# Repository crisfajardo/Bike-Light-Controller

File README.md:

# 🚲 Bike-Light-Controller (Smart Cycling System)

This repository hosts a specialized embedded system designed for conventional bicycles, developed as a final project for my **Bachelor's Degree in Electronic and Telecommunications Engineering**.

The system transforms a standard bike into a "smart" vehicle by automating safety lighting through real-time sensor data fusion.

---

## 🚀 Overview
The **Bike-Light-Controller** manages visibility and signaling automatically. Using an **ESP32-S3** and the **Arduino IDE** framework, the system processes environmental light levels and motion dynamics to ensure rider safety.

### ✨ Key Features
* **Intelligent Brake Light:** Automatically triggers high-intensity rear LEDs when deceleration is detected via the **MPU6050**.
* **Adaptive Headlight:** Adjusts front lighting based on ambient lux levels measured by the **TEMT6000**.
* **Custom Hardware:** Professional PCB designed using **KiCad 9.0**, utilizing official **Espressif hardware libraries** for the ESP32-S3.
* **Real-time Processing:** Low-latency response to motion and lighting changes.

---

## 🛠️ Tech Stack

### Hardware Components
| Component | Function |
| :--- | :--- |
| **MCU** | **ESP32-S3** (Xtensa® 32-bit LX7 Dual-Core) |
| **IMU** | **MPU6050** (6-axis Accelerometer & Gyroscope) |
| **Light Sensor** | **TEMT6000** (High-precision ambient light sensor) |
| **PCB Design** | **KiCad 9.0** (Schematic & Layout) |

### Software & Firmware
* **Language:** C++ / Arduino Framework
* **IDE:** Arduino IDE 2.3.8
* **Communication:** I2C Protocol (Sensors) / MQTT (Optional for IoT telemetry)
* **Libraries:** `Adafruit_MPU6050`, `Adafruit_Sensor`, `Wire.h`

---

## 📂 Repository Structure

```text
├── Firmware/        # Source code (.ino) for the ESP32-S3
├── Hardware/        # KiCad 9.0 Project files (Schematics, PCB, Gerbers)
├── Docs/            # Datasheets, project report, and bibliography
└── Assets/          # Images, circuit diagrams, and 3D renders

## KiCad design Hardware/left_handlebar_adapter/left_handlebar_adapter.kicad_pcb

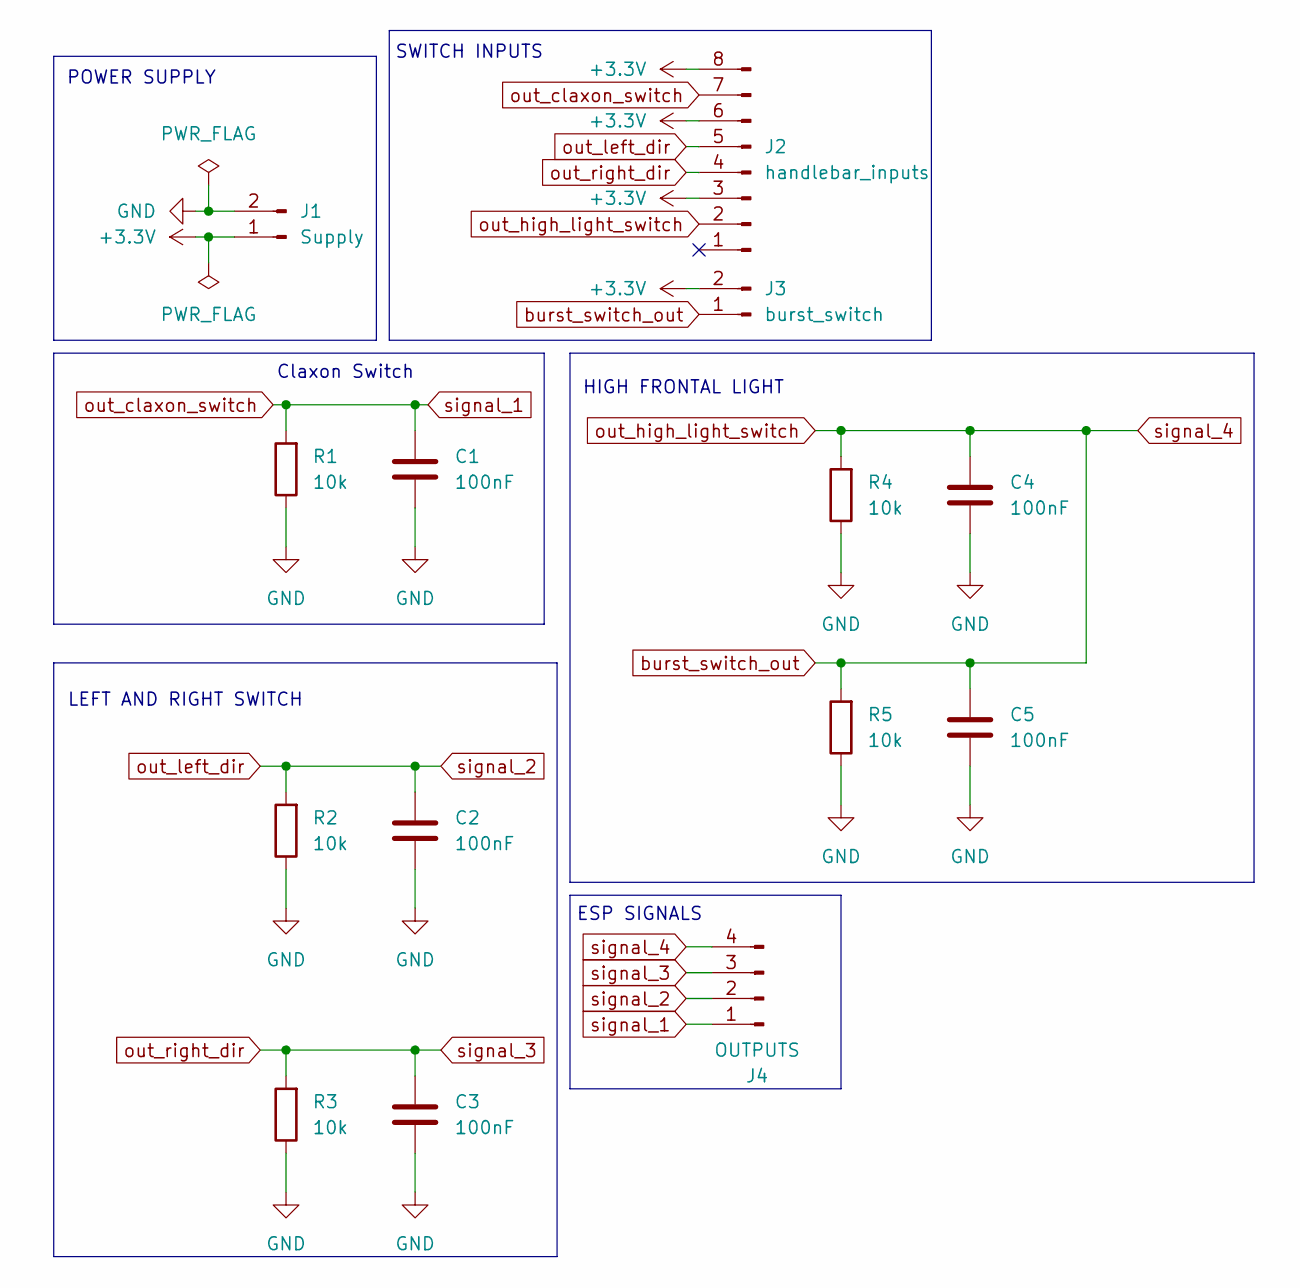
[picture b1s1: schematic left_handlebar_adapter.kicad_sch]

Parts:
C1, C2, C3, C4, C5: 100nF; C_Disc_D5.0mm_W2.5mm_P2.50mm
J1: Supply; PinHeader_1x02_P2.54mm_Vertical
J2: handlebar_inputs; PinHeader_1x08_P2.54mm_Vertical
J3: burst_switch; PinHeader_1x02_P2.54mm_Vertical
J4: OUTPUTS; PinHeader_1x04_P2.54mm_Vertical
R1, R2, R3, R4, R5: 10k; R_Axial_DIN0207_L6.3mm_D2.5mm_P7.62mm_Horizontal

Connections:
+3.3V: J1.1, J2.3, J2.6, J2.8, J3.2
GND: C1.2, C2.2, C3.2, C4.2, C5.2, J1.2, R1.1, R2.1, R3.1, R4.1, R5.1
burst_switch_out: C4.1, C5.1, J2.2, J3.1, J4.4, R4.2, R5.2
out_claxon_switch: C1.1, J2.7, J4.1, R1.2
out_left_dir: C2.1, J2.5, J4.2, R2.2
out_right_dir: C3.1, J2.4, J4.3, R3.2

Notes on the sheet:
POWER SUPPLY
ESP SIGNALS
SWITCH INPUTS
HIGH FRONTAL LIGHT
Claxon Switch
LEFT AND RIGHT SWITCH

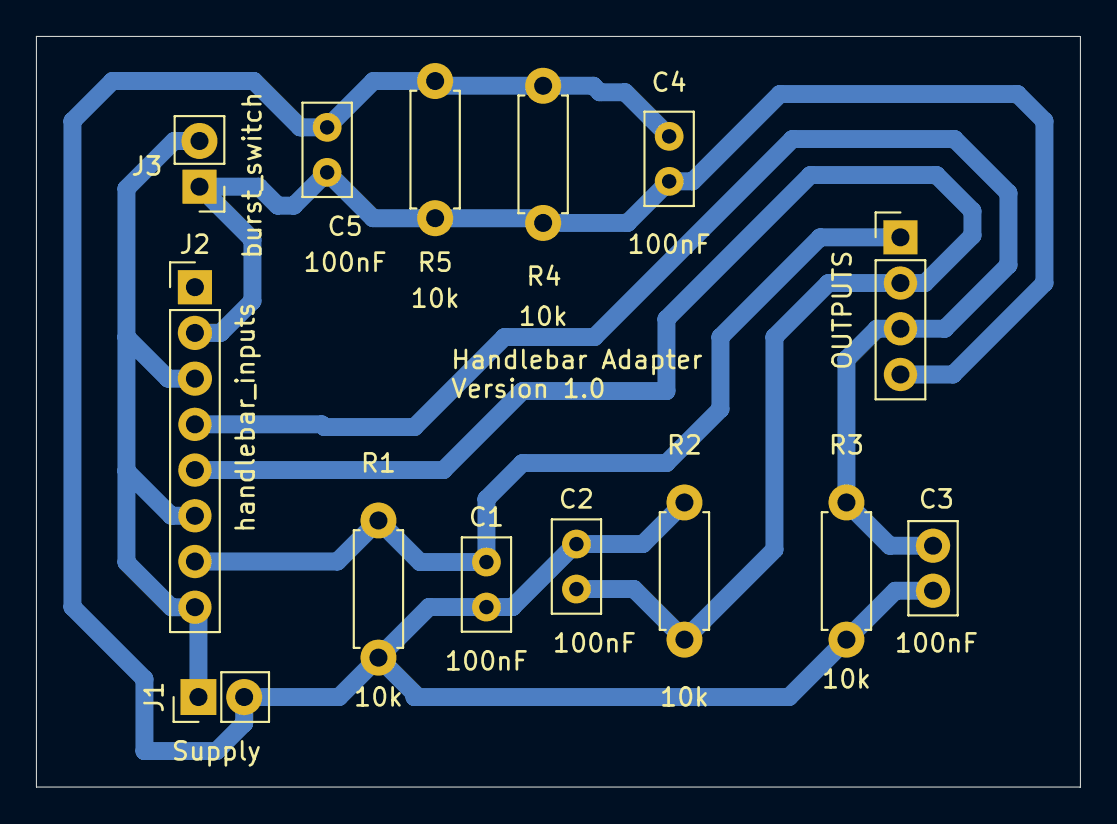
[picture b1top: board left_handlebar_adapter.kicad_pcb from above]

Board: 2 copper layers, 58.0 x 41.7 mm, 14 parts (0 on the bottom side), 6 nets.

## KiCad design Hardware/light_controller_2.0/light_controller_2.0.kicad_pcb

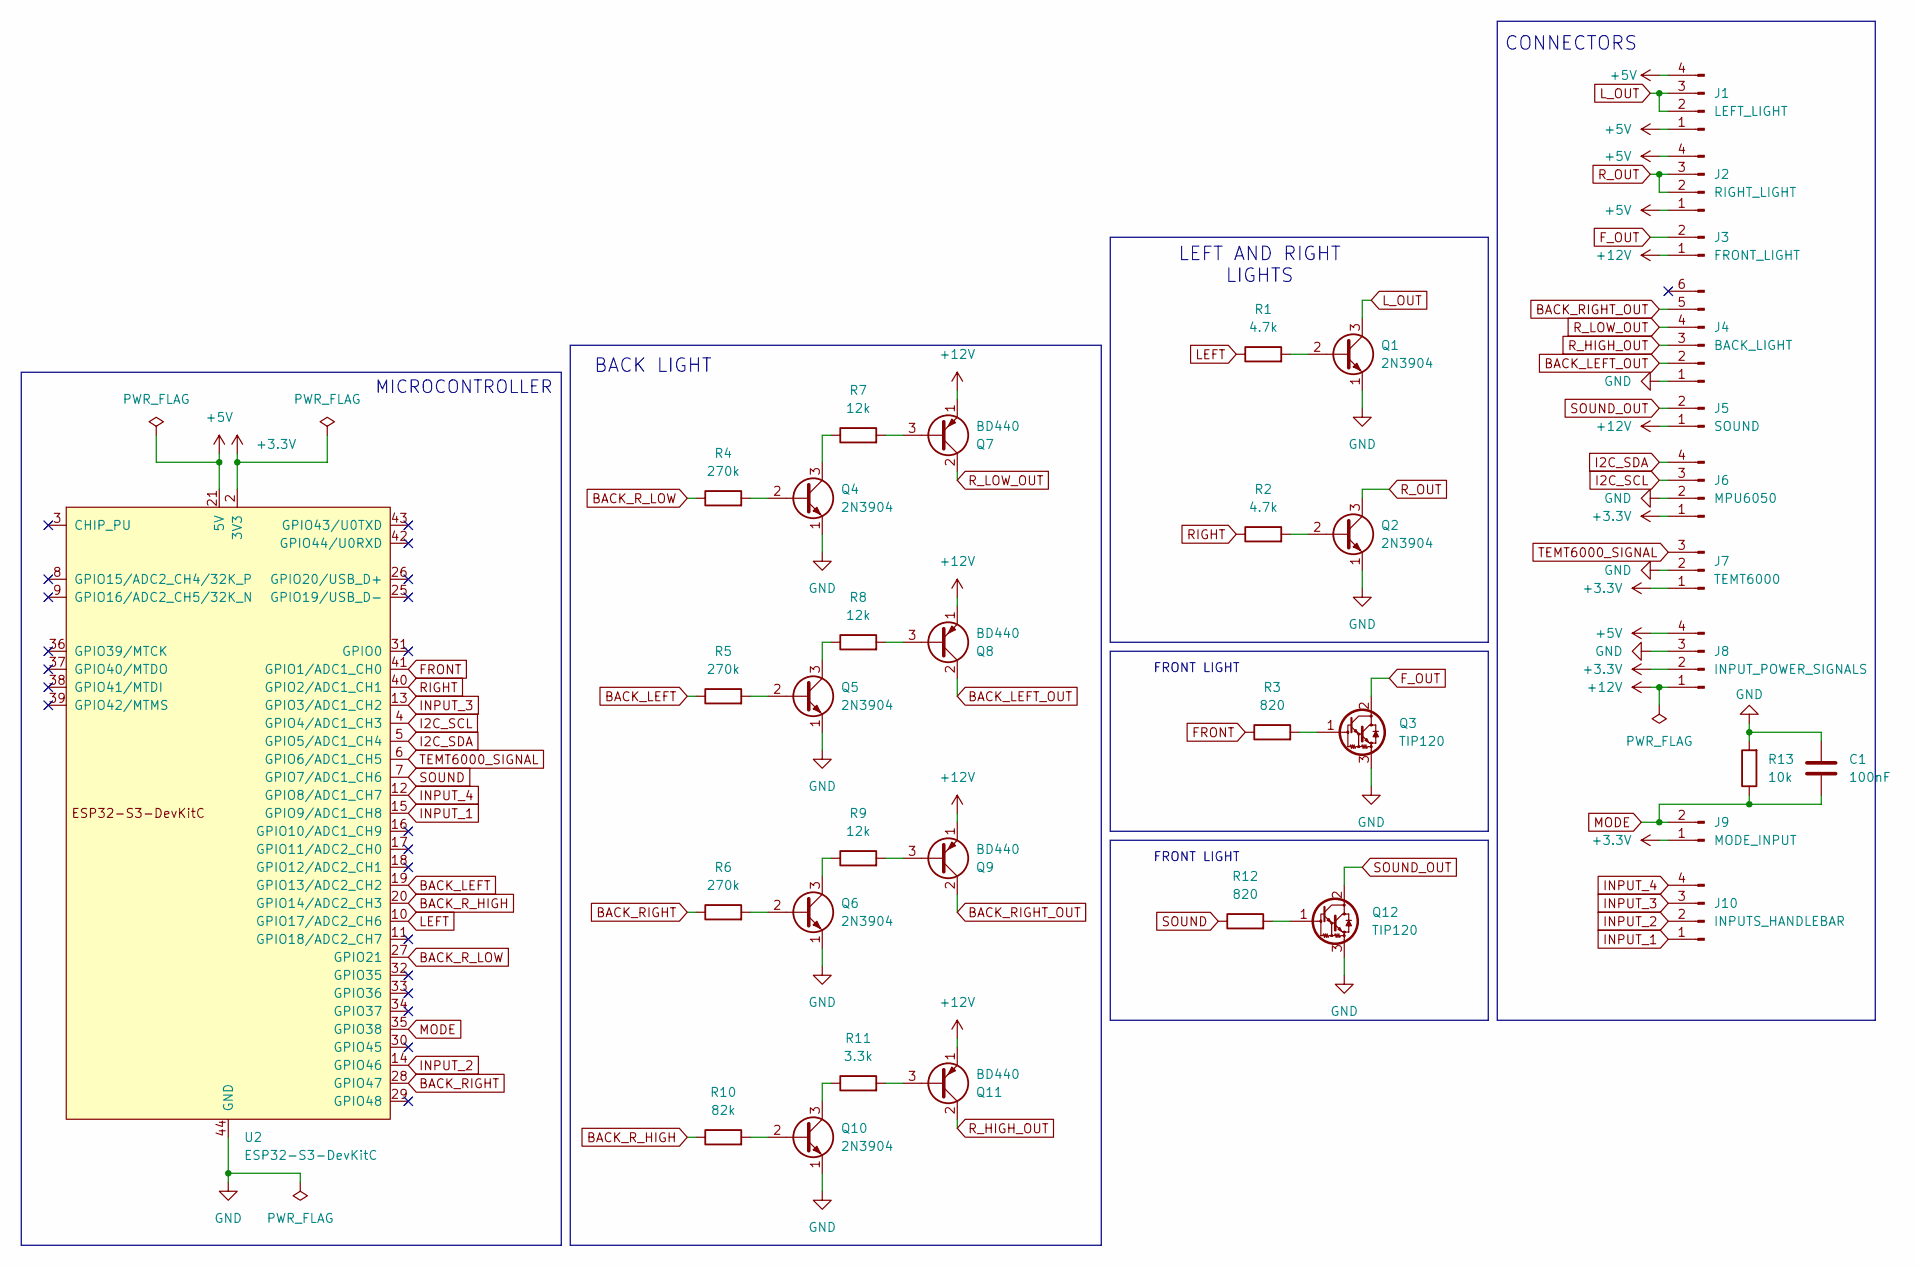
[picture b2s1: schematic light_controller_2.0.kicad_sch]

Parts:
C1: 100nF; C_Disc_D5.0mm_W2.5mm_P2.50mm
J1: LEFT_LIGHT; PinHeader_1x04_P2.54mm_Vertical
J2: RIGHT_LIGHT; PinHeader_1x04_P2.54mm_Vertical
J3: FRONT_LIGHT; PinHeader_1x02_P2.54mm_Vertical
J4: BACK_LIGHT; PinHeader_1x06_P2.54mm_Vertical
J5: SOUND; PinHeader_1x02_P2.54mm_Vertical
J6: MPU6050; PinHeader_1x04_P2.54mm_Vertical
J7: TEMT6000; PinHeader_1x03_P2.54mm_Vertical
J8: INPUT_POWER_SIGNALS; PinHeader_1x04_P2.54mm_Vertical
J9: MODE_INPUT; PinHeader_1x02_P2.54mm_Vertical
J10: INPUTS_HANDLEBAR; PinHeader_1x04_P2.54mm_Vertical
Q1, Q2, Q4, Q5, Q6, Q10: 2N3904; TO-92_Inline_Wide
Q3, Q12: TIP120; TO-220-3_Vertical
Q7, Q8, Q9, Q11: BD440; TO-126-3_Vertical
R1, R2: 4.7k; R_Axial_DIN0207_L6.3mm_D2.5mm_P7.62mm_Horizontal
R3, R12: 820; R_Axial_DIN0207_L6.3mm_D2.5mm_P7.62mm_Horizontal
R4, R5, R6: 270k; R_Axial_DIN0207_L6.3mm_D2.5mm_P7.62mm_Horizontal
R7, R8, R9: 12k; R_Axial_DIN0207_L6.3mm_D2.5mm_P7.62mm_Horizontal
R10: 82k; R_Axial_DIN0207_L6.3mm_D2.5mm_P7.62mm_Horizontal
R11: 3.3k; R_Axial_DIN0207_L6.3mm_D2.5mm_P7.62mm_Horizontal
R13: 10k; R_Axial_DIN0207_L6.3mm_D2.5mm_P7.62mm_Horizontal
U2: ESP32-S3-DevKitC

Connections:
+3.3V: J6.1, J7.1, J8.2, J9.1, U2.1 (3V3), U2.2 (3V3)
+5V: J1.1, J1.4, J2.1, J2.4, J8.4, U2.21 (5V)
+12V: J3.1, J5.1, J8.1, Q7.1 (E), Q8.1 (E), Q9.1 (E), Q11.1 (E)
BACK_LEFT: R5.1, U2.19 (GPIO13/ADC2_CH2)
BACK_LEFT_OUT: J4.2, Q8.2 (C)
BACK_RIGHT: R6.1, U2.28 (GPIO47)
BACK_RIGHT_OUT: J4.5, Q9.2 (C)
BACK_R_HIGH: R10.1, U2.20 (GPIO14/ADC2_CH3)
BACK_R_LOW: R4.1, U2.27 (GPIO21)
FRONT: R3.1, U2.41 (GPIO1/ADC1_CH0)
F_OUT: J3.2, Q3.2 (C)
GND: C1.1, J4.1, J6.2, J7.2, J8.3, Q1.1 (E), Q2.1 (E), Q3.3 (E), Q4.1 (E), Q5.1 (E), Q6.1 (E), Q10.1 (E), Q12.3 (E), R13.2, U2.22 (GND), U2.23 (GND), U2.24 (GND), U2.44 (GND)
I2C_SCL: J6.3, U2.4 (GPIO4/ADC1_CH3)
I2C_SDA: J6.4, U2.5 (GPIO5/ADC1_CH4)
INPUT_1: J10.1, U2.15 (GPIO9/ADC1_CH8)
INPUT_2: J10.2, U2.14 (GPIO46)
INPUT_3: J10.3, U2.13 (GPIO3/ADC1_CH2)
INPUT_4: J10.4, U2.12 (GPIO8/ADC1_CH7)
LEFT: R1.1, U2.10 (GPIO17/ADC2_CH6)
L_OUT: J1.2, J1.3, Q1.3 (C)
MODE: C1.2, J9.2, R13.1, U2.35 (GPIO38)
unnamed: Q1.2 (B), R1.2
unnamed: Q2.2 (B), R2.2
unnamed: Q3.1 (B), R3.2
unnamed: Q4.2 (B), R4.2
unnamed: Q4.3 (C), R7.1
unnamed: Q5.2 (B), R5.2
unnamed: Q5.3 (C), R8.1
unnamed: Q6.2 (B), R6.2
unnamed: Q6.3 (C), R9.1
unnamed: Q7.3 (B), R7.2
unnamed: Q8.3 (B), R8.2
unnamed: Q9.3 (B), R9.2
unnamed: Q10.2 (B), R10.2
unnamed: Q10.3 (C), R11.1
unnamed: Q11.3 (B), R11.2
unnamed: Q12.1 (B), R12.2
RIGHT: R2.1, U2.40 (GPIO2/ADC1_CH1)
R_HIGH_OUT: J4.3, Q11.2 (C)
R_LOW_OUT: J4.4, Q7.2 (C)
R_OUT: J2.2, J2.3, Q2.3 (C)
SOUND: R12.1, U2.7 (GPIO7/ADC1_CH6)
SOUND_OUT: J5.2, Q12.2 (C)
TEMT6000_SIGNAL: J7.3, U2.6 (GPIO6/ADC1_CH5)

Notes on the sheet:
CONNECTORS
LEFT AND RIGHT LIGHTS
MICROCONTROLLER
FRONT LIGHT
BACK LIGHT

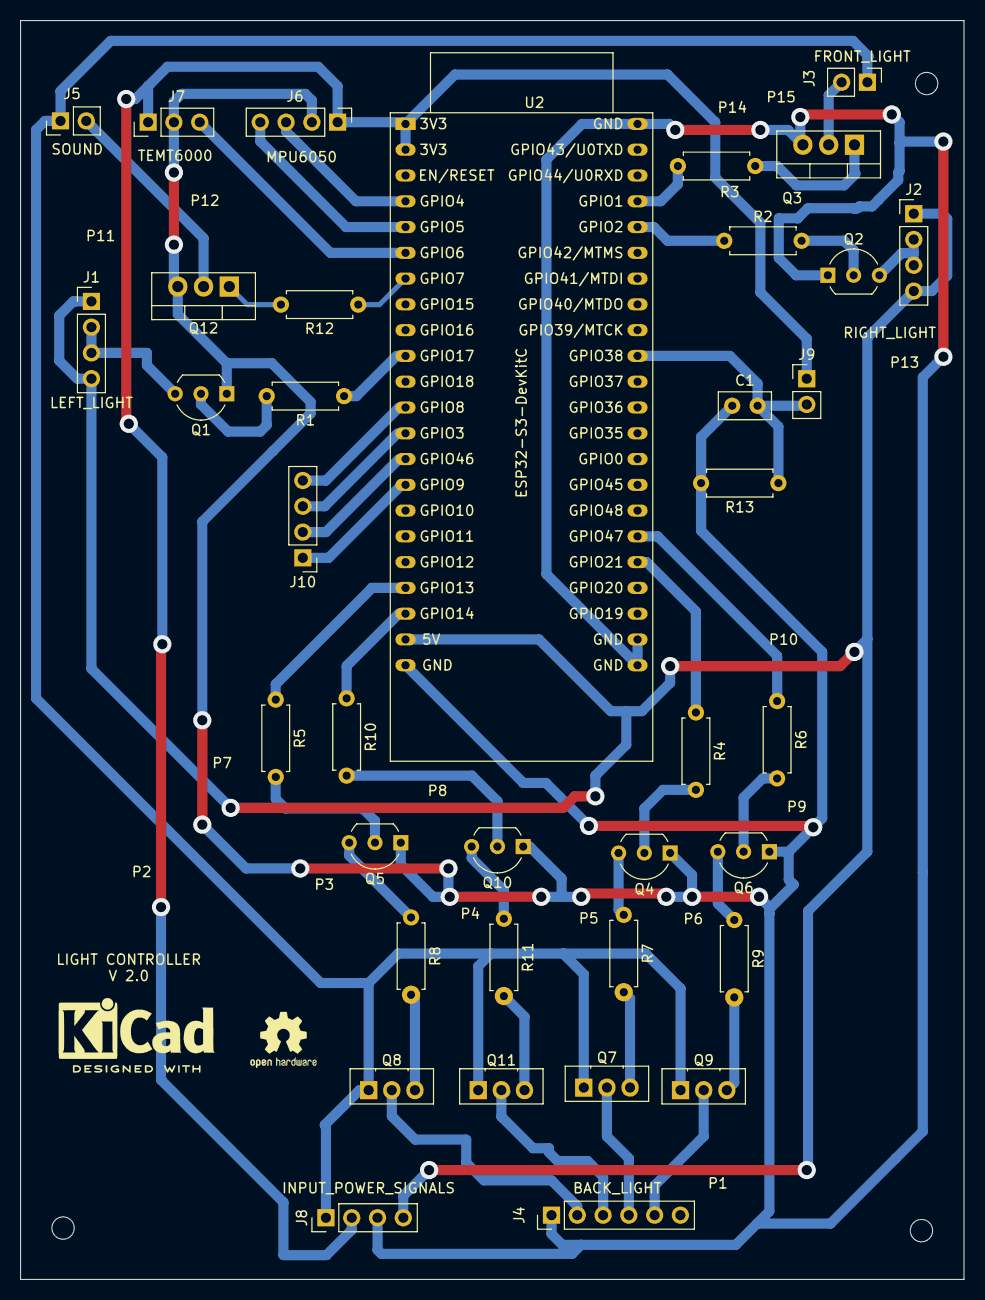
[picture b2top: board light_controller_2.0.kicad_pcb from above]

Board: 2 copper layers, 93.0 x 124.0 mm, 37 parts (0 on the bottom side), 44 nets.

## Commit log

2026-03-26 Revise README for Bike-Light-Controller project
    Updated README to provide detailed project information and features.
2026-03-26 Arduino Sketch and kicad projects added
